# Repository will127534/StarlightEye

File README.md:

# StarlightEye: OpenSource IMX585 Camera Board for Raspberry Pi

## Version 2.0 Changes
Mainly changed the power tree so now it does not require an external 5V input but the board can take all the power from FPC directly, there is a step-up converter that will step it up to 3.6V which is powering both IR filter switch (When used) and 3.3V analog LDO/1.8V Digital LDO input. By doing so the board size can finally shrink down to a perfect 39mm square which also matches the latest OneInchEye.  

The only down side is that the Step-Up convter I'm using here (TPSM83100) is expensive AF, I was going to pick TPSM81033 that is both cheaper and better but I have been waiting it to go on the market for four month now, I don't know when TI will actually get them ship to Mouser so for now I'm stuck with TPSM83100.  

## Introduction
Welcome to the **StarlightEye** project, an open-source camera board designed for Raspberry Pi Compute Module 4 boards using the IMX585. This project aims to provide a high-quality, affordable, and accessible camera module for advanced Raspberry Pi projects. The board is designed using KiCad v6, a popular open-source electronics design automation (EDA) software.

StarlightEye captures stunning high-resolution images and videos with improved low-light performance and dynamic range. It's perfect for photography enthusiasts, developers, and makers who want to level up their Raspberry Pi projects with a powerful camera.  
  
Also see [Quick Start Guide](https://github.com/will127534/StarlightEye/wiki/StarlightEye-Quick-Start-Guide)

## Features
* IMX585 sensor
* **Open-source hardware and software**
* Integrated IR filter switch control via I2C based on CH32V003
* Integrated TMP117 temperature sensor
* Compatible with Raspberry Pi5 and Raspberry Pi Compute Module 4 boards with a 22-pin FPC connector and 4-lane MIPI-CSI (same pinout as Raspberry Pi Compute Module 4 IO Board)
* Limited amount on [https://shop.willwhang.dev/](https://shop.willwhang.dev/) for sell

## Notes
* Gerber and CPL file for JLCPCB is under /Gerber
* [Interactive BOM](https://htmlpreview.github.io/?https://github.com/will127534/StarlightEye/blob/main/bom/ibom.html) [(provided by InteractiveHtmlBom)
](https://github.com/openscopeproject/InteractiveHtmlBom) and JLCPCB BOM under /bom
* Source Code for CH32V003 based I2C controlled IR Filter Switch and Python code on RPI under /software

## Support
For questions, issues, or suggestions, please open an issue in the [GitHub repository](https://github.com/will127534/StarlightEye/issues)

## Schematic

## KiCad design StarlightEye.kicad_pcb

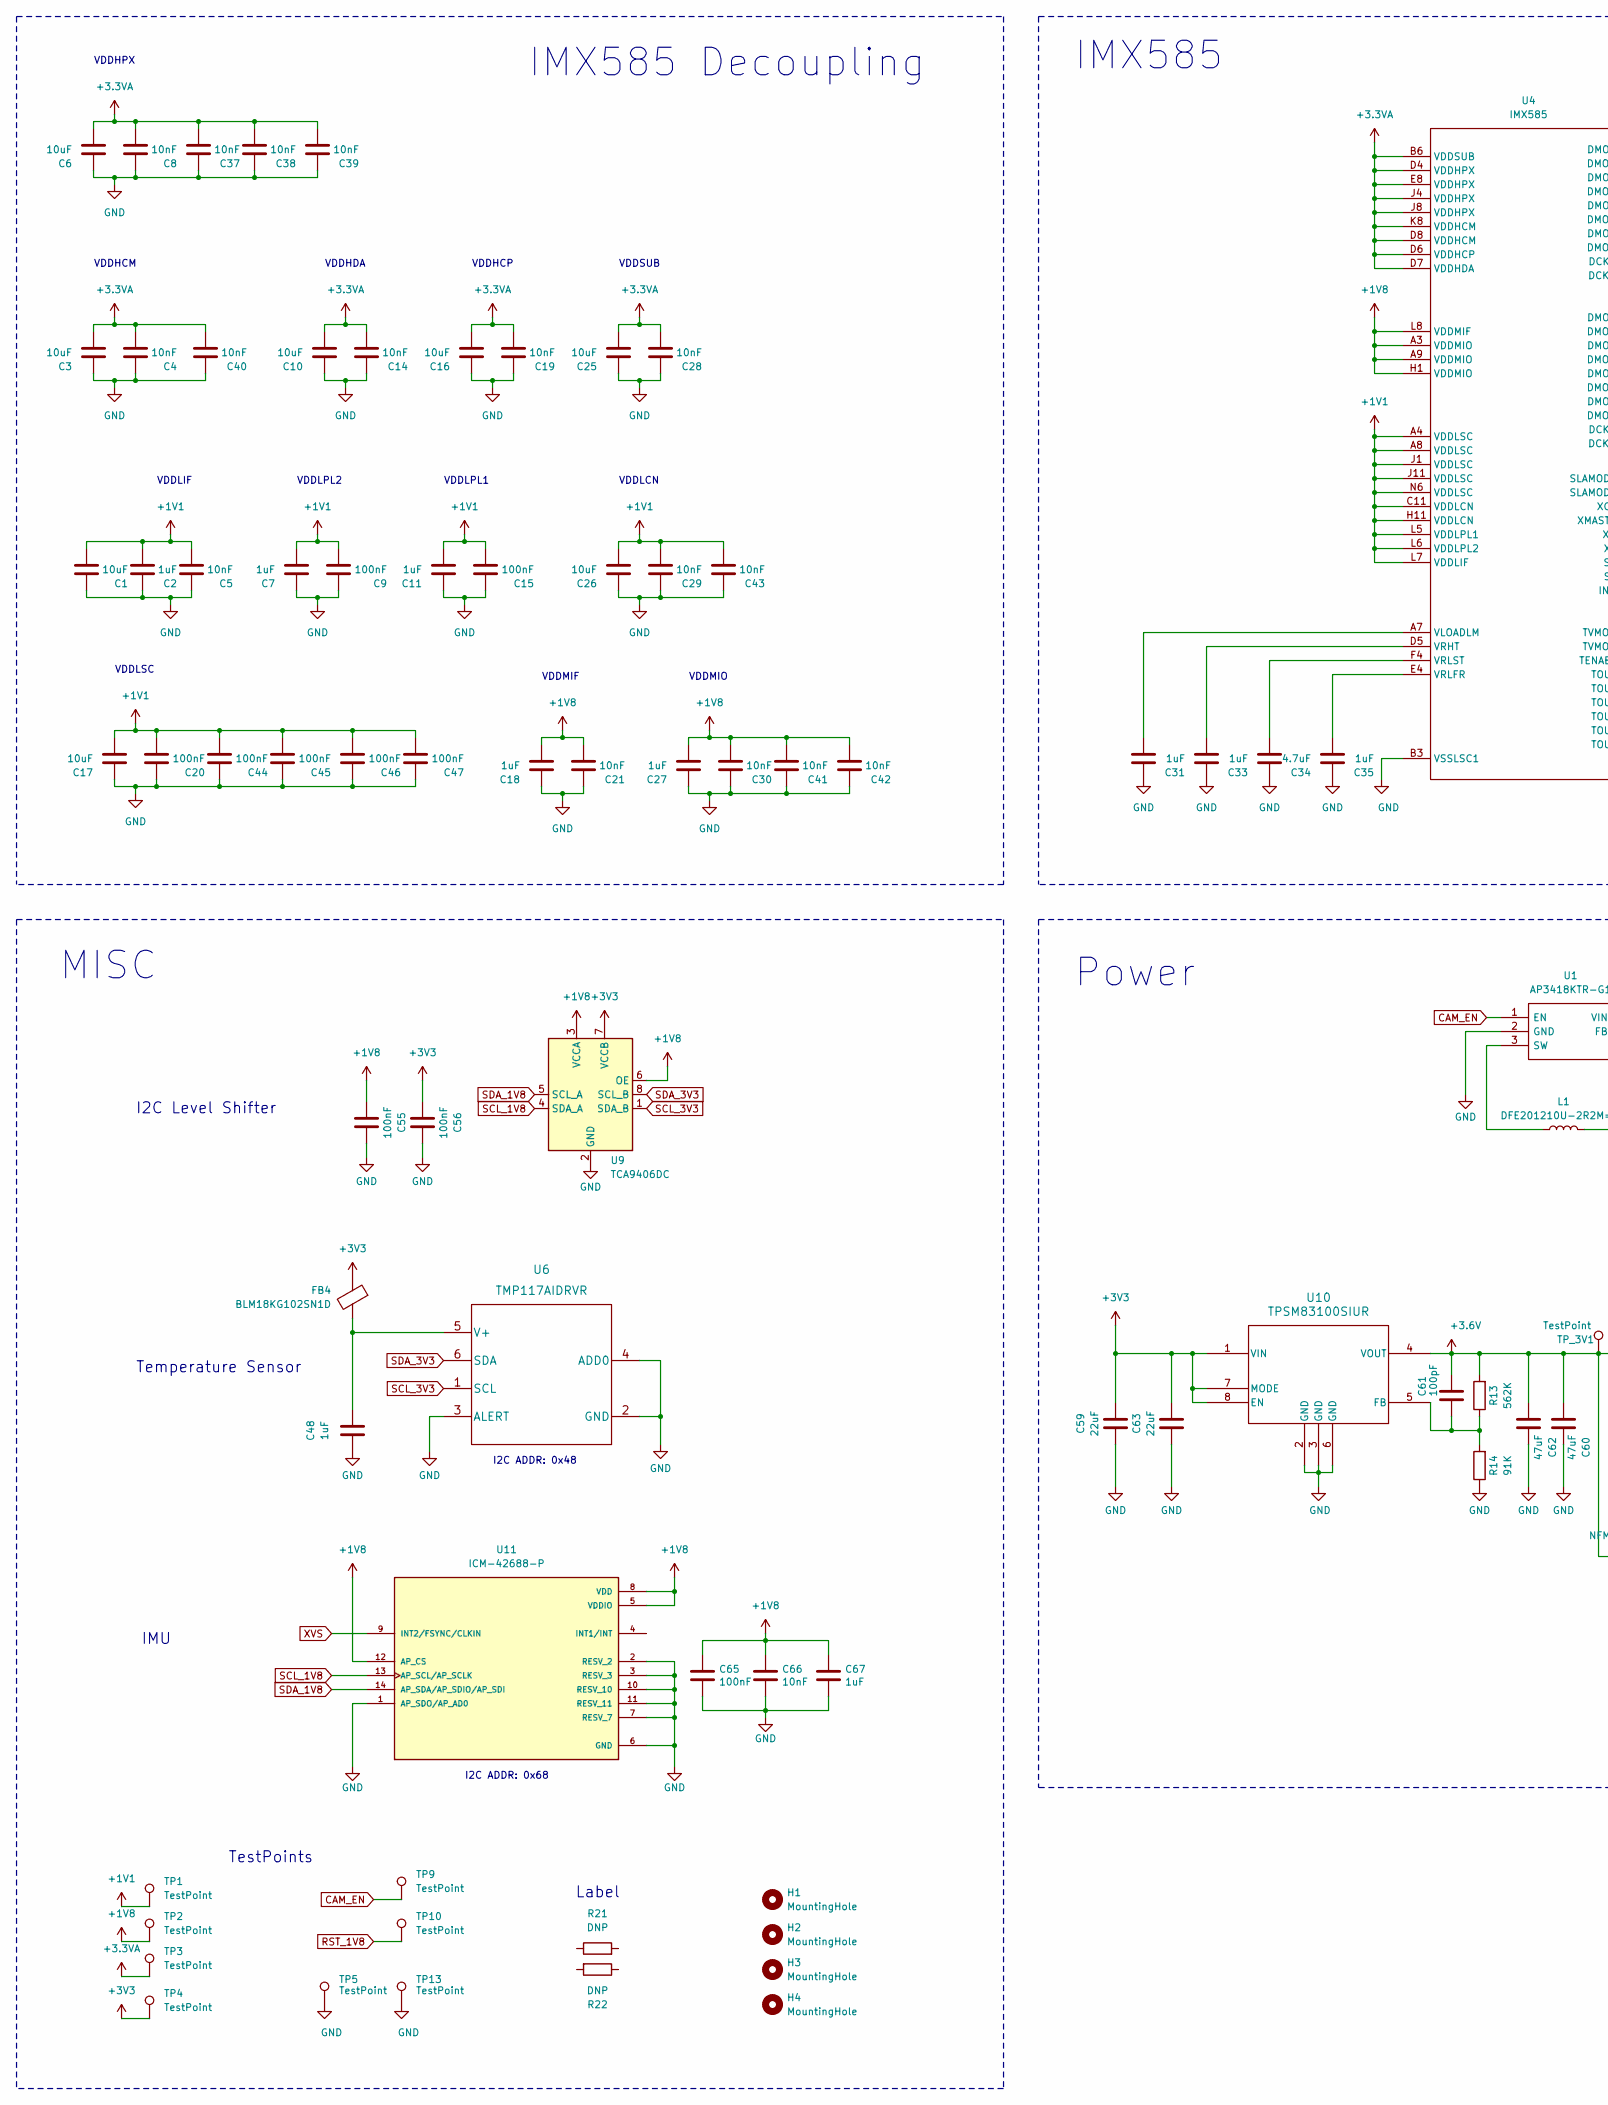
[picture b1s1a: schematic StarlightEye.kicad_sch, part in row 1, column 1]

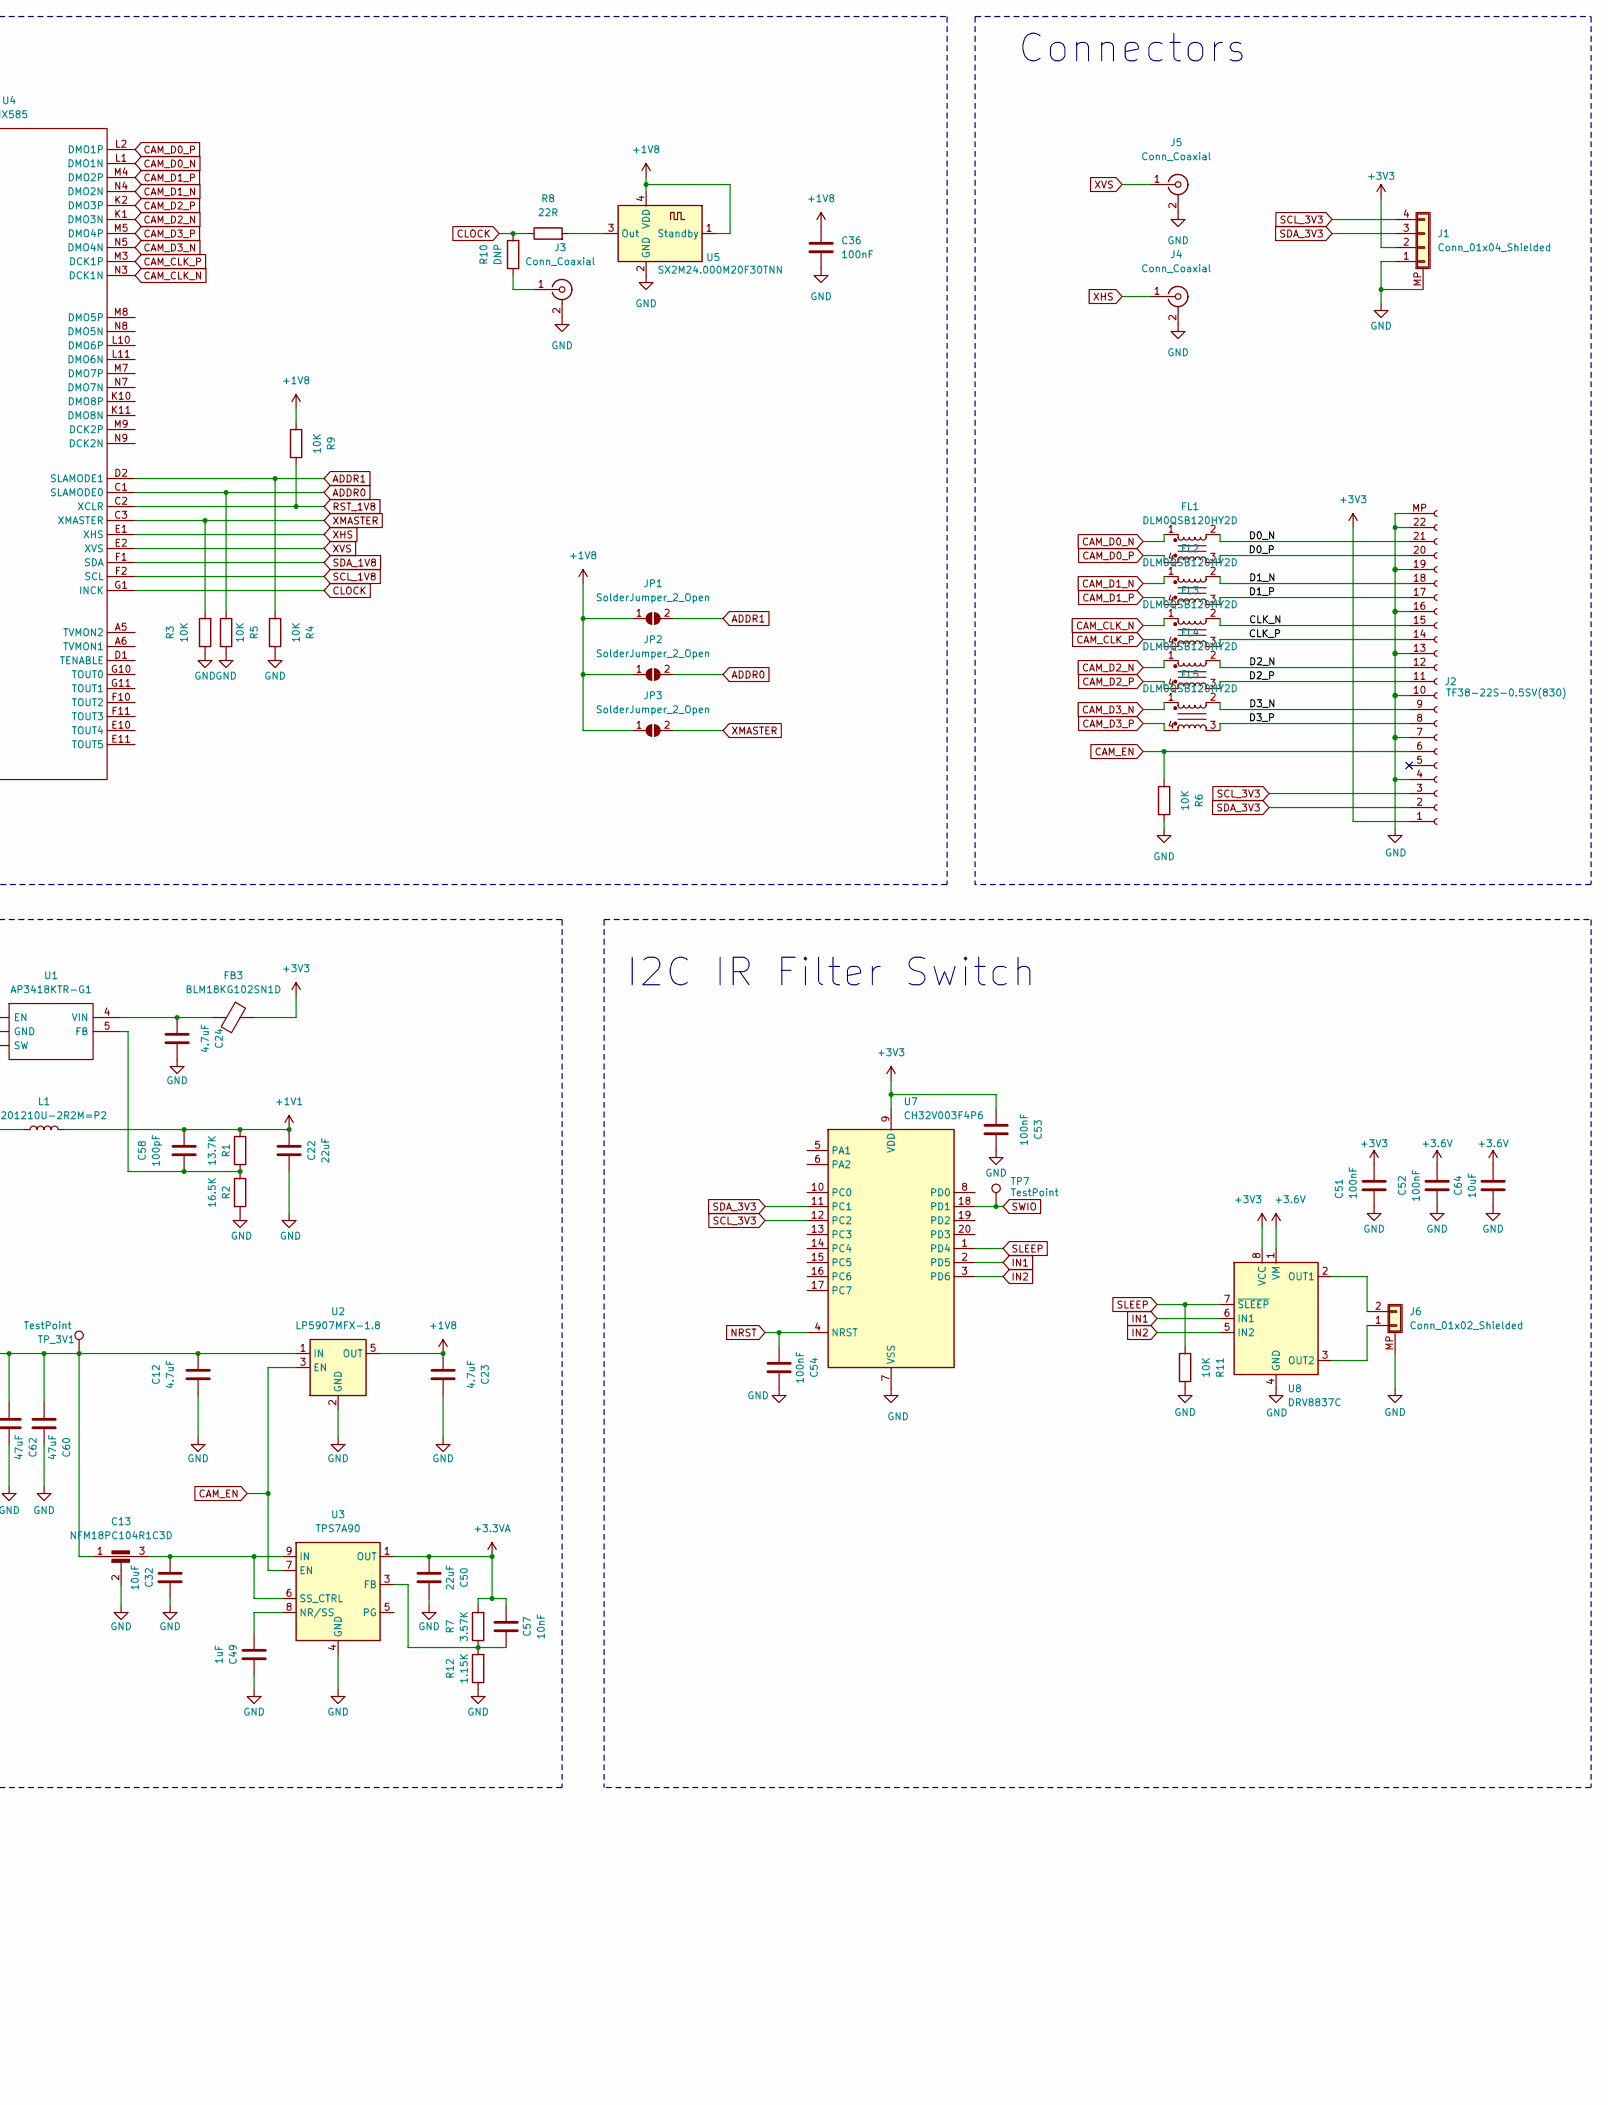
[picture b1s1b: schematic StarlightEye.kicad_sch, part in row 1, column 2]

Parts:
C1, C3, C6, C10, C16, C17, C25, C26: 10uF; C_0402_1005Metric
C2, C7, C11, C18, C27, C31, C33, C35, C48, C49, C67: 1uF; C_0402_1005Metric
C4, C5, C8, C14, C19, C21, C28, C29, C30, C37, C38, C39, C40, C41, C42, C43, C57, C66: 10nF; C_0402_1005Metric
C9, C15, C20, C36, C44, C45, C46, C47, C51, C52, C53, C54, C55, C56, C65: 100nF; C_0402_1005Metric
C12, C23, C24, C34: 4.7uF; C_0603_1608Metric
C13: NFM18PC104R1C3D; NFM18CC101R1C3D
C22, C50, C59, C63: 22uF; C_0603_1608Metric
C32, C64: 10uF; C_0603_1608Metric
C58, C61: 100pF; C_0402_1005Metric
C60, C62: 47uF; C_0603_1608Metric
FB3: BLM18KG102SN1D; L_0603_1608Metric
FB4: BLM18KG102SN1D; L_0402_1005Metric
FL1, FL2, FL3, FL4, FL5: DLM0QSB120HY2D
H1, H2, H3, H4: MountingHole; MountingHole_2.2mm_M2
J1: Conn_01x04_Shielded; JST_SH_BM04B-SRSS-TB_1x04-1MP_P1.00mm_Vertical
J2: TF38-22S-0.5SV(830); TF3822S05SV830; Part Description 22 Position FFC, FPC Connector Contacts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
J3, J4, J5: Conn_Coaxial; U.FL_Hirose_U.FL-R-SMT-1_Vertical
J6: Conn_01x02_Shielded; Molex_PicoBlade_53261-0271_1x02-1MP_P1.25mm_Horizontal
JP1, JP2, JP3: SolderJumper_2_Open; SolderJumper-2_P1.3mm_Open_RoundedPad1.0x1.5mm
L1: DFE201210U-2R2M=P2; L_0805_2012Metric
R1: 13.7K; R_0402_1005Metric
R2: 16.5K; R_0402_1005Metric
R3, R4, R5, R6, R9, R11: 10K; R_0402_1005Metric
R7: 3.57K; R_0402_1005Metric
R8: 22R; R_0402_1005Metric
R10, R21, R22: DNP; R_0402_1005Metric
R12: 1.15K; R_0402_1005Metric
R13: 562K; R_0402_1005Metric
R14: 91K; R_0402_1005Metric
TP1, TP2, TP3, TP4, TP5, TP7, TP9, TP10, TP13: TestPoint; TestPoint_Pad_D1.0mm
TP_3V1: TestPoint; TestPoint_Pad_D1.0mm
U1: AP3418KTR-G1; SOT-23-5; Mouser Part Number 621-AP3418KTR-G1
U2: LP5907MFX-1.8; SOT-23-5
U3: TPS7A90; Texas_S-PDSO-N10_EP1.2x2mm
U4: IMX585; IMX283
U5: SX2M24.000M20F30TNN; Oscillator_SMD_Abracon_ASDMB-4Pin_2.5x2.0mm
U6: TMP117AIDRVR
U7: CH32V003F4P6; TSSOP-20_4.4x6.5mm_P0.65mm
U8: DRV8837C; WSON-8-1EP_2x2mm_P0.5mm_EP0.9x1.6mm
U9: TCA9406DC; TCA9406DCUR
U10: TPSM83100SIUR; MICROSIP8_SIU_TEX-L
U11: ICM-42688-P; PQFN50P300X250X97-14N; PARTREV 1.2

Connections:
+1V1: C1.2, C2.2, C5.2, C7.2, C9.2, C11.2, C15.2, C17.2, C20.2, C22.2, C26.2, C29.2, C43.2, C44.2, C45.2, C46.2, C47.2, C58.2, L1.2, R1.1, TP1.1, U4.A4 (VDDLSC), U4.A8 (VDDLSC), U4.C11 (VDDLCN), U4.H11 (VDDLCN), U4.J1 (VDDLSC), U4.J11 (VDDLSC), U4.L5 (VDDLPL1), U4.L6 (VDDLPL2), U4.L7 (VDDLIF), U4.N6 (VDDLSC)
+1V8: C18.2, C21.2, C23.1, C27.2, C30.2, C36.1, C41.2, C42.2, C55.1, C65.1, C66.1, C67.1, JP1.1 (A), JP2.1 (A), JP3.1 (A), R9.1, TP2.1, U2.5 (OUT), U4.A3 (VDDMIO), U4.A9 (VDDMIO), U4.H1 (VDDMIO), U4.L8 (VDDMIF), U5.1 (Standby), U5.4 (VDD), U9.3 (VCCA), U9.6 (OE), U11.5 (VDDIO), U11.8 (VDD), U11.12 (AP_CS)
+3.3VA: C3.2, C4.2, C6.2, C8.2, C10.2, C14.2, C16.2, C19.2, C25.2, C28.2, C37.2, C38.2, C39.2, C40.2, C50.1, C57.2, R7.2, TP3.1, U3.1 (OUT), U3.2 (OUT), U4.B6 (VDDSUB), U4.D4 (VDDHPX), U4.D6 (VDDHCP), U4.D7 (VDDHDA), U4.D8 (VDDHCM), U4.E8 (VDDHPX), U4.J4 (VDDHPX), U4.J8 (VDDHPX), U4.K8 (VDDHCM)
+3.6V: C12.2, C13.1, C52.2, C60.1, C61.1, C62.1, C64.2, R13.2, TP_3V1.1, U2.1 (IN), U8.1 (VM), U10.4 (VOUT)
+3V3: C51.1, C53.1, C56.1, C59.2, C63.2, FB3.1, FB4.1, J1.2, J2.1, TP4.1, U7.9 (VDD), U8.8 (VCC), U9.7 (VCCB), U10.1 (VIN), U10.7 (MODE), U10.8 (EN)
/CLK_N: FL3.2, J2.15
/CLK_P: FL3.3, J2.14
/D0_N: FL1.2, J2.21
/D0_P: FL1.3, J2.20
/D1_N: FL2.2, J2.18
/D1_P: FL2.3, J2.17
/D2_N: FL4.2, J2.12
/D2_P: FL4.3, J2.11
/D3_N: FL5.2, J2.9
/D3_P: FL5.3, J2.8
ADDR0: JP2.2 (B), R5.1, U4.C1 (SLAMODE0)
ADDR1: JP1.2 (B), R4.1, U4.D2 (SLAMODE1)
CAM_CLK_N: FL3.1, U4.N3 (DCK1N)
CAM_CLK_P: FL3.4, U4.M3 (DCK1P)
CAM_D0_N: FL1.1, U4.L1 (DMO1N)
CAM_D0_P: FL1.4, U4.L2 (DMO1P)
CAM_D1_N: FL2.1, U4.N4 (DMO2N)
CAM_D1_P: FL2.4, U4.M4 (DMO2P)
CAM_D2_N: FL4.1, U4.K1 (DMO3N)
CAM_D2_P: FL4.4, U4.K2 (DMO3P)
CAM_D3_N: FL5.1, U4.N5 (DMO4N)
CAM_D3_P: FL5.4, U4.M5 (DMO4P)
CAM_EN: J2.6, R6.1, TP9.1, U1.1 (EN), U2.3 (EN), U3.7 (EN)
CLOCK: R8.1, R10.2, U4.G1 (INCK)
GND: C1.1, C2.1, C3.1, C4.1, C5.1, C6.1, C7.1, C8.1, C9.1, C10.1, C11.1, C12.1, C13.2, C14.1, C15.1, C16.1, C17.1, C18.1, C19.1, C20.1, C21.1, C22.1, C23.2, C24.2, C25.1, C26.1, C27.1, C28.1, C29.1, C30.1, C31.1, C32.2, C33.1, C34.1, C35.1, C36.2, C37.1, C38.1, C39.1, C40.1, C41.1, C42.1, C43.1, C44.1, C45.1, C46.1, C47.1, C48.1, C49.2, C50.2, C51.2, C52.1, C53.2, C54.2, C55.2, C56.2, C59.1, C60.2, C62.2, C63.1, C64.1, C65.2, C66.2, C67.2, J1.1, J1.MP (Shield), J2.4, J2.7, J2.10, J2.13, J2.16, J2.19, J2.22, J2.MP, J3.2 (Ext), J4.2 (Ext), J5.2 (Ext), J6.MP (Shield), R2.2, R3.1, R4.2, R5.2, R6.2, R11.2, R12.1, R14.1, TP5.1, TP13.1, U1.2 (GND), U2.2 (GND), U3.4 (GND), U3.11 (GND), U4.B3 (VSSLSC1), U4.B4 (VSSLSC2), U4.B8 (VSSLSC3), U4.C5 (VSSHPX4), U4.C6 (VSSHCP5), U4.C7 (VSSHDA6), U4.C8 (VSSHPX7), U4.C10 (VSSLCN8), U4.D3 (VSSHPX9), U4.E3 (VSSHPX10), U4.F3 (VSSHPX11), U4.F8 (VSSHPX12), U4.G2 (VSSLPL213), U4.H2 (VSSLSC14), U4.H4 (VSSHPX15), U4.H8 (VSSHPX16), U4.H10 (VSSLCN17), U4.J2 (VSSLSC18), U4.J10 (VSSLSC19), U4.K3 (VSSLSC20), U4.K5 (VSSLPL121), U4.K6 (VSSLPL222), U4.K7 (VSSHPX23), U4.K9 (VSSLSC24), U4.L3 (VSSLSC25), U4.L9 (VSSLSC26), U4.M6 (VSSLSC27), U5.2 (GND), U6.2 (GND), U6.3 (ALERT), U6.4 (ADD0), U7.7 (VSS), U8.4 (GND), U8.9 (GND), U9.2 (GND), U10.2 (GND), U10.3 (GND), U10.6 (GND), U11.1 (AP_SDO/AP_AD0), U11.2 (RESV_2), U11.3 (RESV_3), U11.6 (GND), U11.7 (RESV_7), U11.10 (RESV_10), U11.11 (RESV_11)
IN1: U7.2 (PD5), U8.6 (IN1)
IN2: U7.3 (PD6), U8.5 (IN2)
NRST: C54.1, U7.4 (NRST)
unnamed: J3.1 (In), R10.1
unnamed: J6.1, U8.3 (OUT2)
unnamed: J6.2, U8.2 (OUT1)
unnamed: C58.1, R1.2, R2.1, U1.5 (FB)
unnamed: L1.1, U1.3 (SW)
unnamed: C24.1, FB3.2, U1.4 (VIN)
unnamed: C57.1, R7.1, R12.2, U3.3 (FB)
unnamed: C49.1, U3.8 (NR/SS)
unnamed: C13.3, C32.1, U3.6 (SS_CTRL), U3.9 (IN), U3.10 (IN)
unnamed: C31.2, U4.A7 (VLOADLM)
unnamed: C33.2, U4.D5 (VRHT)
unnamed: C35.2, U4.E4 (VRLFR)
unnamed: C34.2, U4.F4 (VRLST)
unnamed: R8.2, U5.3 (Out)
unnamed: C48.2, FB4.2, U6.5 (V+)
unnamed: C61.2, R13.1, R14.2, U10.5 (FB)
RST_1V8: R9.2, TP10.1, U4.C2 (XCLR)
SCL_1V8: U4.F2 (SCL), U9.4 (SDA_A), U11.13 (AP_SCL/AP_SCLK)
SCL_3V3: J1.4, J2.3, U6.1 (SCL), U7.12 (PC2), U9.1 (SDA_B)
SDA_1V8: U4.F1 (SDA), U9.5 (SCL_A), U11.14 (AP_SDA/AP_SDIO/AP_SDI)
SDA_3V3: J1.3, J2.2, U6.6 (SDA), U7.11 (PC1), U9.8 (SCL_B)
SLEEP: R11.1, U7.1 (PD4), U8.7 (~SLEEP)
SWIO: TP7.1, U7.18 (PD1)
XHS: J4.1 (In), U4.E1 (XHS)
XMASTER: JP3.2 (B), R3.2, U4.C3 (XMASTER)
XVS: J5.1 (In), U4.E2 (XVS), U11.9 (INT2/FSYNC/CLKIN)

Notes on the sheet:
VDDMIO
VDDLIF
TestPoints
VDDSUB
Connectors
IMU
VDDHPX
VDDLSC
VDDHCM
IMX585
VDDLCN
VDDLPL2
I2C ADDR: 0x48
VDDLPL1
Temperature Sensor
I2C Level Shifter
VDDHDA
IMX585 Decoupling
I2C IR Filter Switch
I2C ADDR: 0x68
VDDHCP
MISC
Power
Label
VDDMIF

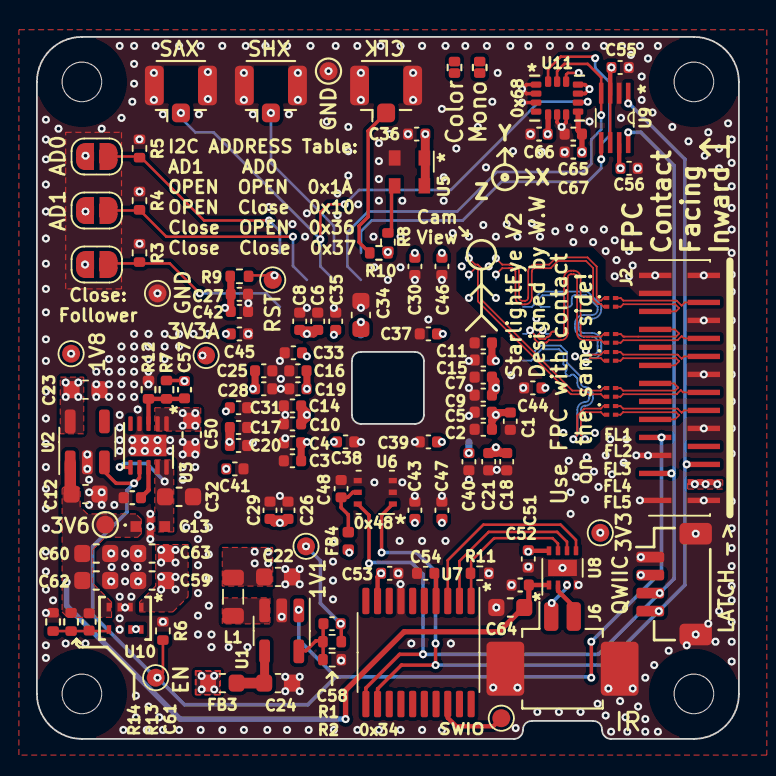
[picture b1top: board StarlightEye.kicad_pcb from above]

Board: 4 copper layers, 39.0 x 39.0 mm, 125 parts (1 on the bottom side), 59 nets.

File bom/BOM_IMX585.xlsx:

Comment | Designator | Footprint | JLCPCB Part #（optional）
NFM18PC104R1C3D | C13 | NFM18CC101R1C3D | C111493
10uF | C25,C26,C6,C10,C1,C16,C17,C3 | C_0402_1005Metric | C15525
1uF | C33,C27,C31,C18,C7,C67,C48,C49,C35,C2,C11 | C_0402_1005Metric | C52923
4.7uF | C34,C24,C23,C12 | C_0603_1608Metric | C19666
10nF | C43,C4,C21,C29,C28,C5,C8,C37,C57,C41,C66,C39,C42,C14,C19,C40,C38,C30 | C_0402_1005Metric | C15195
100nF | C52,C36,C54,C47,C55,C9,C20,C56,C51,C15,C53,C46,C44,C45,C65 | C_0402_1005Metric | C1525
22uF | C59,C50,C22,C63 | C_0603_1608Metric | C59461
47uF | C60,C62 | C_0603_1608Metric | C140782
100pF | C61,C58 | C_0402_1005Metric | C1546
10uF | C64,C32 | C_0603_1608Metric | C96446
BLM18KG102SN1D | FB3 | L_0603_1608Metric | C160982
BLM15PX330SZ1D | FB4 | L_0402_1005Metric | C2661673
DLM0QSB120HY2D | FL4,FL3,FL5,FL1,FL2 | DLM0QSB120HY2D | C3211477
Conn_01x04_Shielded | J1 | JST_SH_BM04B-SRSS-TB_1x04-1MP_P1.00mm_Vertical | C160390
TF38-22S-0.5SV(830) | J2 | TF38-22S-0.5SV(830) | C6552695
Conn_Coaxial | J4,J5,J3 | U.FL_Hirose_U.FL-R-SMT-1_Vertical | C5137195
Conn_01x02_Shielded | J6 | Molex_PicoBlade_53261-0271_1x02-1MP_P1.25mm_Horizontal | C189700
DFE201210U-2R2M=P2 | L1 | L_0805_2012Metric | C2049745
13.7K | R1 | R_0402_1005Metric | C25854
1.15K | R12 | R_0402_1005Metric | C29401
562K | R13 | R_0402_1005Metric | C48838
91K | R14 | R_0402_1005Metric | C4147
16.5K | R2 | R_0402_1005Metric | C25857
10K | R3,R11,R6,R5,R9,R4 | R_0402_1005Metric | C25744
3.57K | R7 | R_0402_1005Metric | C137991
22R | R8 | R_0402_1005Metric | C25092
AP3418KTR-G1 | U1 | SOT-23-5 | C500769
TPSM83100SIUR | U10 | MICROSIP8_SIU_TEX-L | C20346010
ICM-42688-P | U11 | PQFN50P300X250X97-14N | C1850418
LP5907MFX-1.8 | U2 | SOT-23-5 | C92498
TPS7A90 | U3 | Texas_S-PDSO-N10_EP1.2x2mm | C840111
SX2M24.000M20F30TNN | U5 | Oscillator_SMD_Abracon_ASDMB-4Pin_2.5x2.0mm | C2901600
TMP117AIDRVR | U6 | TMP117AIDRVR | C699536
CH32V003F4P6 | U7 | TSSOP-20_4.4x6.5mm_P0.65mm | C5187096
DRV8837C | U8 | WSON-8-1EP_2x2mm_P0.5mm_EP0.9x1.6mm | C191000
TCA9406DC | U9 | TCA9406DCUR | C840107
IMX585 | U4 | IMX283

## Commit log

2023-07-05 init
2023-07-05 adding sch jpg
2023-07-06 Bug fix: swaping part no AP2161W with AP2171W to have the correct EN polarity
2024-03-24 V1.6 init
2024-03-24 A new start
2024-03-24 update readme to v1.6
    Adding I2C IR filter code
    Update PCBA images
    chmod +x on IRFilter
    Update images
    Update README.md
2024-04-26 Update to the correct v1.6 gerber
2024-10-02 V1.7
2025-07-26 Ver 2.0 HW
2025-07-26 Update Image
2026-06-28 Change purchase link in README
    Updated the link for purchasing to the new shop URL.
